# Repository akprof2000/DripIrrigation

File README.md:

# 🌱 Капельный полив на ESP32

Автономная система капельного полива для дачного участка: 8 независимых каналов, автополив по влажности почвы, учёт расхода воды и контроль засора фильтра. Управление — полностью через Telegram-бота, без облаков и сторонних приложений ([библиотеки Alex Gyver](https://github.com/GyverLibs)).

## 📑 Оглавление

- [Возможности](#возможности)
- [Состав системы](#состав-системы)
  - [Компоненты](#компоненты)
  - [Схема подключения](#схема-подключения)
  - [Распиновка ESP32](#распиновка-esp32)
- [Установка](#установка)
- [Первый запуск](#первый-запуск)
- [Руководство пользователя](#руководство-пользователя)
  - [Команды бота](#команды-бота)
  - [Роли пользователей](#роли-пользователей)
  - [Структура меню](#структура-меню)
  - [Статус системы](#статус-системы)
  - [Типовые сценарии](#типовые-сценарии)
- [Как работает автоматика](#как-работает-автоматика)
- [Данные на SD-карте](#данные-на-sd-карте)
- [Справочник по пунктам меню](#справочник-по-пунктам-меню)
- [Обновление прошивки (OTA)](#обновление-прошивки-ota)
- [Лицензия](#лицензия)

## Возможности

- 🌿 **8 независимых каналов**: клапан + ёмкостный датчик влажности почвы на каждый
- 🤖 **Управление через Telegram** — настройка, статус, отчёты, до 8 пользователей с ролями
- 💧 **Автополив по влажности** с гистерезисом; режимы «всегда ВКЛ», «всегда ВЫКЛ», «авто», «парник»
- 🔧 **Авто-калибровка границ** датчиков: диапазон сам расширяется под реальные условия, разовые выбросы отфильтровываются
- 🌙 **Погодные блокировки**: ночь и дождь (настраиваются)
- 📟 **Датчик потока**: расход за сессию и накопленный итог, текущая скорость в статусе
- 🧽 **Контроль засора фильтра**: тревога в Telegram при падении потока ниже порога
- 💪 **Нагнетательный насос**: пусковой режим + удержание по числу открытых клапанов
- 🗑️ **Пролив дренажа** после простоя, 🚰 **заливка бака** на ночь
- 📊 **Журналы CSV** на SD-карте, графики и отчёты прямо в чате
- 📤 **OTA-обновление** прошивки файлом через Telegram

## Состав системы

### Компоненты

| Компонент | Назначение |
|-----------|------------|
| ESP32 (DevKit) | контроллер |
| SD-карта, модуль 3.3 В | конфигурация, журналы CSV, отчёты |
| Кнопка (подтянута к земле) | сброс настроек |
| Датчик освещённости (дискретный) | определение дня/ночи |
| Датчик дождя (дискретный) | блокировка полива в дождь |
| Датчик потока YF-S201 (~450 имп/л) | учёт расхода и контроль фильтра, ставится на общую магистраль |
| DS3231 (I2C) | часы реального времени, синхронизация с NTP |
| PCF8574 (I2C, адрес 0x20) | расширитель портов для 8 клапанов |
| Релейный модуль, 8 каналов | управление клапанами полива |
| Реле ×3 | нагнетательный насос, налив ёмкости, пролив дренажа |
| 74HC4051 | аналоговый мультиплексор датчиков влажности |
| Ёмкостные датчики влажности ×8 | по одному на канал |

### Плата-носитель

Готовая печатная плата, в которую все модули вставляются в гнёзда, а внешние провода заходят на винтовые
клеммники: [описание платы](docs/hardware-carrier-board.md), [список покупок](docs/bom.md),
[пошаговая сборка](docs/assembly.md). Исходники платы и генератор — в папке `hardware/`.

### Схема подключения

### Распиновка ESP32

| GPIO | Подключение | GPIO | Подключение |
|------|-------------|------|-------------|
| 2 | встроенный светодиод (индикация) | 18 | SD-карта · SCK |
| 4 | датчик освещённости | 19 | SD-карта · MISO |
| 5 | SD-карта · CS | 21 | I2C · SDA (DS3231, PCF8574) |
| 12 | 74HC4051 · S0 | 22 | I2C · SCL (DS3231, PCF8574) |
| 13 | 74HC4051 · S1 | 23 | SD-карта · MOSI |
| 14 | 74HC4051 · S2 | 25 | реле пролива дренажа |
| 15 | датчик дождя | 26 | реле нагнетательного насоса |
| 16 | кнопка сброса настроек | 27 | датчик потока YF-S201 |
| 17 | реле налива ёмкости | 33 | АЦП — сигнал мультиплексора |

## Установка

**Потребуется:** Wi-Fi сеть с выходом в интернет и созданный Telegram-бот ([инструкция по созданию бота](https://kit.alexgyver.ru/tutorials/telegram-basic/)).

1. Соберите схему
2. Скачайте исходники репозитория
3. Токен бота можно задать двумя способами (начиная с v1.8.0):
   - **ничего не делать** — при первом запуске устройство само попросит токен на странице настройки WiFi и сохранит его в EEPROM (так работают готовые бинарники из релизов);
   - **вшить в прошивку** — скопировать `secrets.example.h` в `secrets.h` и вписать токен (файл не коммитится в git).
4. Прошейте ESP32 (Arduino IDE или arduino-cli, плата `esp32`)

> ⚠️ У бота в @BotFather пропишите список команд:
> ```
> reset - сброс состояния
> control - управление поливом
> status - текущий статус
> pause - остановка статусных сообщений
> continue - продолжение получения сообщений
> ```

## Первый запуск

1. **Настройка Wi-Fi.** При первом старте устройство поднимает собственную Wi-Fi точку. Подключитесь к ней — откроется страница настройки: выберите домашнюю сеть, введите пароль и **токен бота** (если он не вшит в прошивку). После сохранения устройство перезагрузится.

   > 🔐 Токен хранится в EEPROM. Если он уже сохранён, поле «Токен» можно оставить пустым — значение не изменится. А если прошивка окажется без токена (например, взята из релизов), устройство при старте поднимет портал **только для его ввода**: сеть, пользователи и калибровки при этом сохраняются, и работа продолжится с того же места.
2. **Регистрация владельца.** Напишите боту кодовое слово со страницы настройки — вы становитесь владельцем устройства.
3. **Базовая настройка** через меню бота:
   - режимы работы клапанов → [сценарий](#типовые-сценарии);
   - калибровка датчиков влажности;
   - названия культур по каналам;
   - пороги срабатывания.
4. Система готова к работе.

> ⚠️ Запомните кодовую фразу со страницы настройки Wi-Fi — без неё не зарегистрироваться владельцем.

> 💡 Сброс к заводским настройкам: зажмите кнопку на 3 секунды сразу после старта и дождитесь трёх коротких миганий светодиода.

## Руководство пользователя

### Команды бота

| Команда | Действие | Кому доступна |
|---------|----------|---------------|
| [`/reset`](#reset) | сброс состояния меню, стартовое меню | всем зарегистрированным |
| [`/control`](#controls) | меню управления поливом | всем зарегистрированным |
| [`/status`](#status) | текущий статус системы и датчиков | всем зарегистрированным |
| [`/pause`](#pause) | остановить статусные сообщения | всем зарегистрированным |
| [`/continue`](#continue) | возобновить статусные сообщения | всем зарегистрированным |
| `/register` | запрос на регистрацию | незарегистрированным |

### Роли пользователей

| Роль | Как получить | Что доступно |
|------|--------------|--------------|
| 👑 Владелец | первым вводит кодовое слово с портала настройки | всё + OTA-обновление; не может быть понижен или удалён |
| 🎭 Администратор | назначается через «Пользователи → Повышение» | управление, настройка, пользователи, перезагрузка |
| 👤 Пользователь | отправляет `/register`, админ подтверждает | управление поливом, статус, отчёты |

### Структура меню

Пункты с пометкой 👑 видят только администраторы и владелец.

- 👑 [Перезагрузка](#restart)
- 👑 [Пользователи](#users) → [Список](#userslist) · [Повышение](#usersup) · [Понижение](#usersdown) · [Удаление](#usersdel)
- [Управление](#controls)
  - [Режим работы](#working) · [Названия](#naiming) · [Пороги срабатывания](#borders)
  - [Расход воды](#waterflow) · [Пролив дренажа](#spillage) · [Поиск датчика](#search)
- [Статус](#status)
- [Отчёты](#reports)
  - [Графики](#graphics) → [за вчера](#graphystd) · [за сегодня](#graphtd) · [за декаду](#graphdec) · [за период](#graphp) · [за дату](#graphc)
  - [Файл за вчера](#fileystd) · [Файл текущий](#filetd) · [Файл за дату](#filec)
- 👑 [Настройка](#settings)
  - [Работа ночью](#workatnight) · [Работа под дождём](#workatrain)
  - [Дельта влажности](#deltahum) · [Дельта калибровки](#deltacb)
  - [Авто-калибровка без задержки](#autocalnodelay)
  - [Насос давления](#boostpump) · [Порог фильтра](#clogthreshold) · [Фильтр прочищен](#filterclean)
  - [Таймаут Telegram](#tgtimeout)
  - [Калибровка](#calibrate) · [Ручная калибровка](#calibrateManual)
  - [Сброс настроек](#restore) · [Удаление файлов](#filesdel)

### Статус системы

`/status` показывает полную картину одним сообщением:

| Блок | Содержимое |
|------|-----------|
| 📅 Дата и время | текущее время системы (NTP + RTC) |
| 🌙/☀️ Погода | день или ночь, идёт ли дождь |
| 🌱 По каждому каналу | название культуры, влажность %, порог %, состояние клапана, режим работы (владельцу дополнительно — сырое значение АЦП) |
| 💧 Расход воды | литры за текущую сессию и накопленный итог |
| 🧽 Фильтр | текущая скорость потока, эталон, порог тревоги, состояние (норма/засор) |
| 💪 Насос давления | работает сейчас или нет **и почему** (пусковой режим / порог клапанов / дренаж), текущая настройка |
| 💾 Память | свободная память контроллера |

### Типовые сценарии

<details>
<summary><b>🚿 Настроить автополив канала</b></summary>

1. `Управление → Режим работы` → выбрать клапан → `🤖 АВТО` (или `🏠 А.П.` для парника — поливает и в дождь)
2. `Управление → Пороги срабатывания` → выбрать клапан → ввести порог влажности в %. Клапан откроется при влажности ниже «порог − дельта» и закроется выше «порог + дельта» — [как это работает](#полив-по-влажности)
3. `Управление → Названия` → дать каналу имя культуры («🍅 Томаты»)
</details>

<details>
<summary><b>🔧 Откалибровать датчик влажности</b></summary>

1. `Настройка → Калибровка` → выбрать датчик
2. Опустить датчик в воду → `➡️ ДАЛЕЕ` (это 100 % влажности)
3. Вытереть насухо → `➡️ ДАЛЕЕ` (это 0 %)
4. Установить датчик в почву → `✅ ЗАВЕРШИТЬ`

Если известны точные значения АЦП — `Настройка → Ручная калибровка`, ввести пару `мин,макс`.
</details>

<details>
<summary><b>🔍 Найти датчик, если неизвестен его номер</b></summary>

`Управление → Поиск датчика`: замер в воде, затем насухо — бот назовёт номер датчика с наибольшей разницей показаний.
</details>

<details>
<summary><b>💧 Посмотреть расход воды</b></summary>

`Управление → Расход воды` — литры за текущую сессию полива и накопленный итог, там же кнопка стирания данных. Текущая скорость потока — в `Статусе`.
</details>

<details>
<summary><b>🧽 Пришла тревога «засорился фильтр»</b></summary>

1. Перекройте воду и прочистите фильтр на магистрали
2. `Настройка → Фильтр прочищен` — система заново замерит скорость «чистого» потока

Подробнее о механизме — [Контроль засора фильтра](#учёт-расхода-и-контроль-засора-фильтра).
</details>

<details>
<summary><b>💪 Настроить насос повышения давления</b></summary>

`Настройка → Насос давления`:
- число **1–8** — держать насос включённым, пока открыто столько клапанов и больше;
- **9** — не держать, только пусковые 30 секунд при каждом открытии клапана.

Текущее состояние насоса и причина — в `Статусе`. [Диаграмма работы](#насос-повышения-давления).
</details>

<details>
<summary><b>📈 Получить графики и файлы измерений</b></summary>

`Отчёты → Графики` — график влажности по каналам за вчера/сегодня/декаду/период/дату.
`Отчёты → Файл...` — бот пришлёт CSV-файл с измерениями ([формат](#данные-на-sd-карте)).
</details>

<details>
<summary><b>🔕 Отключить уведомления на время</b></summary>

Команда `/pause`, вернуть — `/continue` (действует до перезагрузки устройства).
</details>

<details>
<summary><b>👥 Добавить нового пользователя</b></summary>

1. Новый человек пишет боту `/register`
2. Администраторам приходит запрос со ссылкой-командой — админ нажимает её, человек зарегистрирован как «пользователь»
3. При необходимости повысить: `Пользователи → Повышение`
</details>

<details>
<summary><b>📤 Обновить прошивку по воздуху</b></summary>

Владелец отправляет в чат файл `DripIrrigation.ino.bin` — устройство обновится и перезагрузится. [Подробнее](#обновление-прошивки-ota).
</details>

## Как работает автоматика

Общая картина: раз в минуту выполняется цикл полива, а фоновые задачи (бот, насос, контроль потока, дренаж, связь) работают непрерывно.

### Полив по влажности

Раз в минуту система опрашивает все 8 датчиков (медиана из 9 замеров АЦП — устойчиво к помехам) и для каждого канала в режиме «авто» сравнивает влажность с порогом. Гистерезис (зона ±Δ вокруг порога) исключает дребезг — клапан не щёлкает туда-сюда при колебаниях показаний:

### Авто-калибровка границ

Со временем реальный диапазон датчика уходит за границы, заданные при калибровке: почва после ливня оказывается влажнее «воды» из стакана, а в засуху — суше «сухого» замера. Тогда проценты упираются в 0 или 100 и перестают что-либо показывать.

Система расширяет границы сама: если показание вышло за границу, она отодвигается до этого значения **с запасом в дельту калибровки**. Границы только расширяются, сужения нет — сузить можно лишь перекалибровкой.

Два предохранителя:

- **Разовые выбросы игнорируются.** Граница двигается, только если превышение держится **3 минутных замера подряд**. Один сбойный отсчёт АЦП (наводка, плохой контакт) обнуляет счётчик и ничего не портит. Внутри окна подтверждения берётся самое мягкое из превышений, чтобы выброс не утянул границу. Отключается настройкой [«Авто-калибровка без задержки»](#autocalnodelay).
- **Во время калибровки функция выключена.** Пока открыт диалог калибровки или поиска датчика, датчик держат в воде или на воздухе — такие показания нельзя принимать за рабочие, иначе система «выучит» калибровочные экстремумы как норму.

Новые границы сохраняются на SD-карту автоматически.

### Аварийный режим при неисправном оборудовании

Платы (RTC, SD-карта, расширитель клапанов PCF8574) инициализируются **неблокирующе**: если узел не отвечает, система всё равно завершает загрузку и поднимает бота. Неисправность приходит в чат с пояснением последствий — не нужно ехать к устройству и подключаться кабелем, чтобы понять, что случилось.

Пока неисправность не устранена:

- **полив остановлен** — работать с неисправным железом опасно;
- насос, дренаж и залив бака **выключены напрямую по пинам** (не через возможно мёртвый PCF8574);
- интерфейс бота свёрнут до отчёта и **единственной кнопки «Перезагрузка»** — починив контакт, систему можно поднять прямо из чата.

### Погодные блокировки

Ночью и в дождь полив останавливается, если это запрещено в настройках. Исключения: каналы «всегда ВКЛ» и режим «парник» продолжают полив под дождём (но не ночью). При наступлении ночи подаётся сигнал заполнения ёмкости — за ночь вода прогреется к утреннему поливу.

### Насос повышения давления

При открытии любого клапана насос включается минимум на 30 секунд для стабилизации давления. Дальше — по настройке: либо выключается, либо продолжает работать, пока открыто N и более клапанов:

Пролив дренажа также идёт с включённым насосом. Фактическое состояние насоса и причина всегда видны в `Статусе`.

### Пролив дренажа

Если полив не шёл более 5 часов, при открытии первого клапана автоматически запускается пролив дренажа на 12 секунд — сброс накопившейся ржавчины из труб, чтобы не засорялись форсунки. Ручной запуск: `Управление → Пролив дренажа`.

### Учёт расхода и контроль засора фильтра

На общей магистрали стоит импульсный датчик потока (YF-S201). Система считает расход за сессию полива и накопленный итог, а также непрерывно следит за скоростью потока:

Ключевые детали алгоритма:

- после открытия клапана трубы наполняются — поток кратковременно завышен, поэтому система **дожидается стабилизации** и только потом замеряет;
- эталон «чистого» фильтра запоминается автоматически (разовые выбросы отфильтровываются — новое значение должно продержаться несколько минут);
- замеры при работающем пусковом насосе и заливке бака не учитываются;
- тревога подтверждается несколькими окнами замера подряд и повторяется не чаще раза в сутки.

## Данные на SD-карте

```
/configuration.dat      — конфигурация системы (бинарная)
/ГГГГ/ММ/ДД.csv         — журнал измерений за день
```

Каждую минуту в CSV дописывается по строке на канал:

| Колонка | Описание |
|---------|----------|
| `UnixTime` | метка времени UNIX |
| `DateTime` | дата и время в читаемом виде |
| `Index` | номер канала (1–8) |
| `Title` | название культуры |
| `Humidity` | влажность, % |
| `Valve` | состояние клапана: 1 — открыт, 0 — закрыт |
| `Border` | порог срабатывания, % |
| `Night` | ночь: 1/0 |
| `Rain` | дождь: 1/0 |

Файлы за прошлые годы можно удалить из бота: `Настройка → Удаление файлов`.

## Справочник по пунктам меню

#### /reset — сброс состояния
Сбрасывает состояние меню и выводит стартовое меню

#### /status · меню «Статус»
Полный статус системы — [расшифровка блоков](#статус-системы)

#### /pause — остановка статусных сообщений
Останавливает сообщения о событиях на устройстве (действует до перезагрузки)

#### /continue — продолжение получения сообщений
Возобновляет сообщения о событиях

#### 👑 Перезагрузка
Перезапускает устройство (с подтверждением)

#### 👑 Пользователи

- **Список** — зарегистрированные пользователи (идентификаторы и роли)
- **Повышение** — Пользователь → Администратор
- **Понижение** — Администратор → Пользователь (владельца понизить нельзя)
- **Удаление** — удаление пользователя (владельца удалить нельзя)

#### Управление

- **Режим работы** — режим каждого клапана: ✅ постоянно включен · ⛔ постоянно выключен · 🤖 автоматический по влажности · 🏠 парник (авто, работает и при дожде); кнопка «Установить для всех»
- **Названия** — имя выращиваемой культуры для каждого канала
- **Пороги срабатывания** — порог влажности каждого клапана в %
- **Расход воды** — литры за сессию и накопленный итог; стирание данных
- **Пролив дренажа** — ручной запуск пролива (12 секунд)
- **Поиск датчика** — определить номер датчика по замерам в воде и насухо

#### Отчёты

- **Графики**
  - **за вчера** — почасовой график влажности по каналам
  - **за сегодня** — почасовой график за текущий день
  - **за декаду** — последние 10 дней, 6 значений в сутки
  - **за период** — от 1 до 60 дней, `целое(60 / кол-во дней)` значений в сутки
  - **за дату** — график за выбранный день
- **Файл за вчера** — CSV-файл с измерениями за вчера
- **Файл текущий** — CSV-файл за сегодня
- **Файл за дату** — CSV-файл за выбранный день

#### 👑 Настройка

- **Работа ночью** — разрешить/запретить полив ночью
- **Работа под дождём** — разрешить/запретить полив в дождь
- **Дельта влажности** — половина гистерезиса вокруг порога, % (0–100, по умолчанию 5)
- **Дельта калибровки** — запас у границ калибровки датчиков, ед. АЦП (0–2048, по умолчанию 15). Используется и как запас при [авто-калибровке границ](#авто-калибровка-границ)
- **Авто-калибровка без задержки** — двигать границу сразу по первому замеру за ней. По умолчанию **выключено**: граница двигается, только если превышение держится 3 замера подряд (3 мин) — так одиночный выброс АЦП не портит калибровку. Включайте, только если нужна мгновенная реакция
- **Насос давления** — держать насос при ≥ N открытых клапанах (1–8); 9 — только пусковые 30 с
- **Порог фильтра** — % от скорости «чистого» фильтра, ниже которого тревога (10–90, по умолчанию 50)
- **Фильтр прочищен** — сброс эталона после чистки, система замерит его заново
- **Таймаут Telegram** — через сколько секунд без связи считать её потерянной (120–3600, по умолчанию 180). Увеличьте, если приходит много сообщений о кратковременных обрывах связи
- **Калибровка** — пошаговая калибровка датчика: замер в воде, затем насухо
- **Ручная калибровка** — ввод граничных значений АЦП парой `мин,макс`
- **Сброс настроек** — возврат к заводским установкам
- **Удаление файлов** — удаление архивов измерений за прошлые годы

## Обновление прошивки (OTA)

1. Возьмите готовый файл со [страницы релизов](https://github.com/akprof2000/DripIrrigation/releases) (собирается автоматически в GitHub Actions) — или соберите сами (`Скетч → Экспорт бинарного файла` в Arduino IDE):
   - `DripIrrigation.ino.bin` — обычный (~1.3 МБ);
   - `DripIrrigation.ino.bin.gz` — сжатый (~0.8 МБ), удобнее по мобильному интернету — устройство распакует его само.
2. Отправьте файл в чат боту **от имени владельца**
3. Устройство скачает файл, обновится и перезагрузится; после старта придёт сообщение «🚀 Система запущена! Прошивка vX.Y.Z»

> 💡 Имя файла может содержать суффикс копии, который добавляет Windows при повторном скачивании: `DripIrrigation.ino.bin (2).gz` и `DripIrrigation.ino (2).bin` тоже принимаются — переименовывать не нужно.

> 🔁 Если пришло `OTA Fetch Error` — файл не удалось **скачать** (обычно не хватило памяти на защищённое соединение после долгой работы). Прошивка при этом не пострадала: просто отправьте файл ещё раз, а если повторяется — перезагрузите систему через меню и повторите.

> ✅ Проверить версию можно в любой момент — она указана в шапке `/status`. Если после OTA номер не изменился, обновление не применилось.

> 🛡️ OTA безопасен: прошивка пишется в неактивный раздел, загрузка переключается только при валидном образе. Неудачное обновление оставит устройство на прежней прошивке (не «кирпич»).

> ⚠️ Прошивка должна быть собрана под ту же схему разделов (partition scheme), что и установленная.

> 🏷️ Версия задаётся в `version.h` (`FW_VERSION`) и должна совпадать с git-тегом релиза.

## Сторонние компоненты

- Библиотеки [Alex Gyver](https://github.com/GyverLibs): FastBot2, GyverNTP, GyverDS3231, FileData, CharDisplay и зависимости
- [uzlib](https://github.com/pfalcon/uzlib) (zlib-лицензия) — потоковая распаковка gzip для OTA из `.gz` (файлы `uzlib.h`, `tinflate.c`, `tinfgzip.c`, `crc32.c`, `adler32.c` и заголовки)
- PCF8574 library (Renzo Mischianti)

## Лицензия

[WTFPL 2.0](LICENSE) — делайте с этим кодом что хотите, без каких-либо условий.

Исключение: файлы `uzlib.h`, `tinflate.c`, `tinfgzip.c`, `crc32.c`, `adler32.c`,
`defl_static.h`, `tinf.h`, `tinf_compat.h`, `uzlib_conf.h` — это стороннее
заимствование ([uzlib](https://github.com/pfalcon/uzlib)) и они остаются под
своей zlib-лицензией; уведомления об авторстве в них сохранены.

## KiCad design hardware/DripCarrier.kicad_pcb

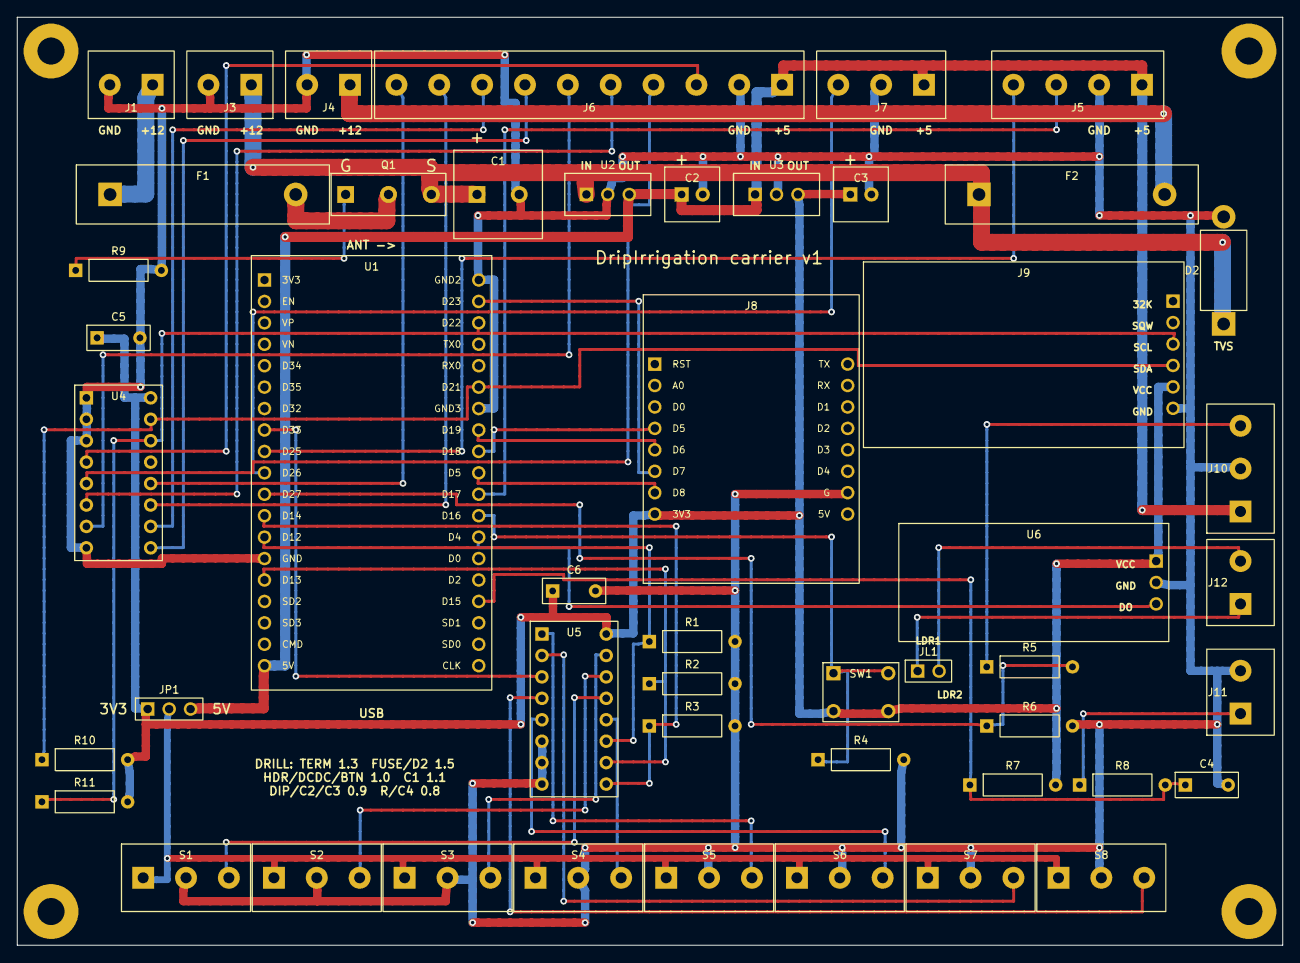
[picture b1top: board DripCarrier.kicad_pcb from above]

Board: 2 copper layers, 150.0 x 110.0 mm, 53 parts (0 on the bottom side), 46 nets.

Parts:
C1: 1000u/16V; CAP_P5
C2, C3: 100u; CAP_P25
C4, C5, C6: 100n; CAP_C5
D2: P6KE18CA; DO201
F1: F1 5A; FUSE5x20
F2: F2 3A; FUSE5x20
H1, H2, H3, H4: M3; HOLE
J1: 12V IN; TERM2
J3: 12V VALVES; TERM2
J4: 12V PUMP; TERM2
J5: RELAY 2: +5 GND FILL DRAIN; TERM4
J6: RELAY 8: +5 GND IN1..IN8; TERM10
J7: RELAY 1: +5 GND PUMP; TERM3
J8: SD D1 mini; D1MINI
J9: DS3231; DS3231MOD
J10: FLOW; TERM3
J11: RAIN SW; TERM2
J12: LDR; TERM2
JL1: LDR; HDR1x2
JP1: 3V3 SENS 5V; JMP1x3
Q1: IRF4905; TO220_2
R1, R2, R3, R4, R5, R7, R9: 10k; R_AX
R6: 33k; R_AX
R8: 1k; R_AX
R10, R11: 4.7k; R_AX
S1: SOIL 1; TERM3
S2: SOIL 2; TERM3
S3: SOIL 3; TERM3
S4: SOIL 4; TERM3
S5: SOIL 5; TERM3
S6: SOIL 6; TERM3
S7: SOIL 7; TERM3
S8: SOIL 8; TERM3
SW1: RESET CFG; BTN6x6
U1: ESP32 DevKitC 38; ESP32_38
U2: DC-DC 12-5V 2A; TO220
U3: DC-DC 5-3.3V; TO220
U4: PCF8574P; DIP16
U5: 74HC4051; DIP16
U6: LIGHT LM393; LM393MOD

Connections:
12V_F: F1.2, Q1.2
12V_PUMP: F2.2, J4.1
12V_RAW: F1.1, J1.1
+3V3: C3.1, C5.1, C6.1, J8.3V3, J9.5, JP1.1, R7.2, R10.2, R11.2, SW1.3, SW1.4, U3.3, U4.16, U5.16, U6.1
+5V: C2.1, J5.1, J6.1, J7.1, J10.1, JP1.3, U1.5V, U2.3, U3.1
+12V: C1.1, D2.1, F2.1, J3.1, Q1.3, U2.1
ADC: U1.D33, U5.3
BTN: R4.1, SW1.1, SW1.2, U1.D16
DRAIN: J5.4, U1.D25
FILL: J5.3, U1.D17
FLOW: R5.2, R6.1, U1.D27
FLOW_IN: J10.3, R5.1
GND: C1.2, C2.2, C3.2, C4.2, C5.2, C6.2, D2.2, J1.2, J3.2, J4.2, J5.2, J6.2, J7.2, J8.G, J9.6, J10.2, J11.2, R1.2, R2.2, R3.2, R4.2, R6.2, R9.2, S1.2, S2.2, S3.2, S4.2, S5.2, S6.2, S7.2, S8.2, U1.GND, U1.GND2, U1.GND3, U2.2, U3.2, U4.1, U4.2, U4.3, U4.8, U5.6, U5.7, U5.8, U6.2
LDR_A: J12.1, JL1.1
LDR_B: J12.2, JL1.2
LIGHT: U1.D4, U6.3
P0: J6.3, U4.4
P1: J6.4, U4.5
P2: J6.5, U4.6
P3: J6.6, U4.7
P4: J6.7, U4.9
P5: J6.8, U4.10
P6: J6.9, U4.11
P7: J6.10, U4.12
PUMP: J7.3, U1.D26
QG: Q1.1, R9.1
RAIN: C4.1, R7.1, R8.2, U1.D15
RAIN_IN: J11.1, R8.1
S0: R1.1, U1.D12, U5.11
S1: R2.1, U1.D13, U5.10
S2: R3.1, U1.D14, U5.9
SCL: J9.3, R11.1, U1.D22, U4.14
SDA: J9.4, R10.1, U1.D21, U4.15
SD_CS: J8.D8, U1.D5
SD_MISO: J8.D6, U1.D19
SD_MOSI: J8.D7, U1.D23
SD_SCK: J8.D5, U1.D18
SENS_V: JP1.2, S1.1, S2.1, S3.1, S4.1, S5.1, S6.1, S7.1, S8.1
Y0: S1.3, U5.13
Y1: S2.3, U5.14
Y2: S3.3, U5.15
Y3: S4.3, U5.12
Y4: S5.3, U5.1
Y5: S6.3, U5.5
Y6: S7.3, U5.2
Y7: S8.3, U5.4

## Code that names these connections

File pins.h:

// pins.h 📌 Назначение пинов ESP32 (аппаратная карта проекта)
#pragma once

#define PIN_SPI_CS 5            // 💾 CS SD-карты

const int LED_BUILTIN = 2;     // 💡 Встроенный светодиод
const int BUTTON = 16;         // 🔘 Кнопка сброса настроек
const int LIGHT = 4;           // ☀️ Датчик освещённости (день/ночь)
const int RAIN = 15;           // 🌧️ Датчик дождя
const int FILL = 17;           // 🚰 Клапан наполнения бака
const int DRAIN = 25;          // 🗑️ Клапан слива (дренаж)
const int PUMP = 26;           // ⚡ Реле насоса
const int FLOW_SENSOR = 27;    // 💧 Датчик потока воды (расходомер)

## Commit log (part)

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2023-06-29 feat: первый раз добавил проект
2023-06-30 feat: полная обработка сценариев полива первый комит
2023-07-01 fix: ошибка полной инициализации, идинтефикация режимов, сдвиг при переходе
2023-07-01 chore: добавлен файл версионности и настройки
2023-07-01 1.0.0
2023-07-23 fix: добавил вотч дог, а то повисает
2023-07-23 1.0.1
2024-03-23 first add esp23 irrigation code
2024-04-12 reconnect wifi and get date time
2024-04-15 сделал все меню настройки
2024-04-15 add calibration sensors
2024-04-20 add file data writer
2024-04-21 first final version
2024-04-21 bug fix, init array
2024-04-22 report by messages
2024-04-22 add graph for decade
2024-04-22 bug fix delta hum
2024-04-22 first add code
2024-04-23 vug fix timeout WDT
2024-04-23 bug fix, change timeout WDT, add period reports
2024-04-23 bug fix
2024-04-23 bug dix
2024-04-23 bug fix, text on graph
2024-04-23 add delete history by year
2024-04-23 add function delete old records by year
2024-05-11 fix rain variable, add enable / disable valve now on config
2024-05-14 fix WDT, fix write to file, change menu reports
2024-05-15 fix menu
2024-05-17 add reports as main menu
2024-05-18 first full test version
2024-05-19 edit read me
2024-05-19 аdd block schema
2024-05-19 visio save
2024-05-28 fix found index
2024-05-30 fix by new version arduino ide and esp32
2024-06-04 Add auto filling by night
2024-06-04 add night filling and bug fix
2024-06-05 small fix
2024-06-05 add manual calibrate
2024-06-06 add work in rain if auto greenhouse
2024-06-09 change reset to start
2024-06-10 add get data on manual calibrate
2024-06-26 small bug fix
2024-06-27 fix web name config
2024-07-02 add drenage
2024-07-04 add check WiFi before send and reading
2024-07-04 add check WiFI status before send message, bug fix
2024-07-04 fix internet broken
2024-07-04 fix WiFi recconect
2024-07-04 fix resend inside message
2024-07-09 add manual drenage
2024-07-12 fix time connection
2024-07-14 add text on start day on rain continue
2025-06-14 feat: добавил полноеуправление клапанами мелкие багофиксы
2025-06-14 feat: full manage switchs
2025-06-14 1.1.0
2026-05-31 change fsatbot to fastbot2
2026-06-03 Add flow control
2026-06-04 add pump for 7 and 8 valves
2026-06-09 change code from kimi@
2026-06-10 fix add components
